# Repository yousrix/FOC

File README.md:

# FOC
bldc driver for foc motor

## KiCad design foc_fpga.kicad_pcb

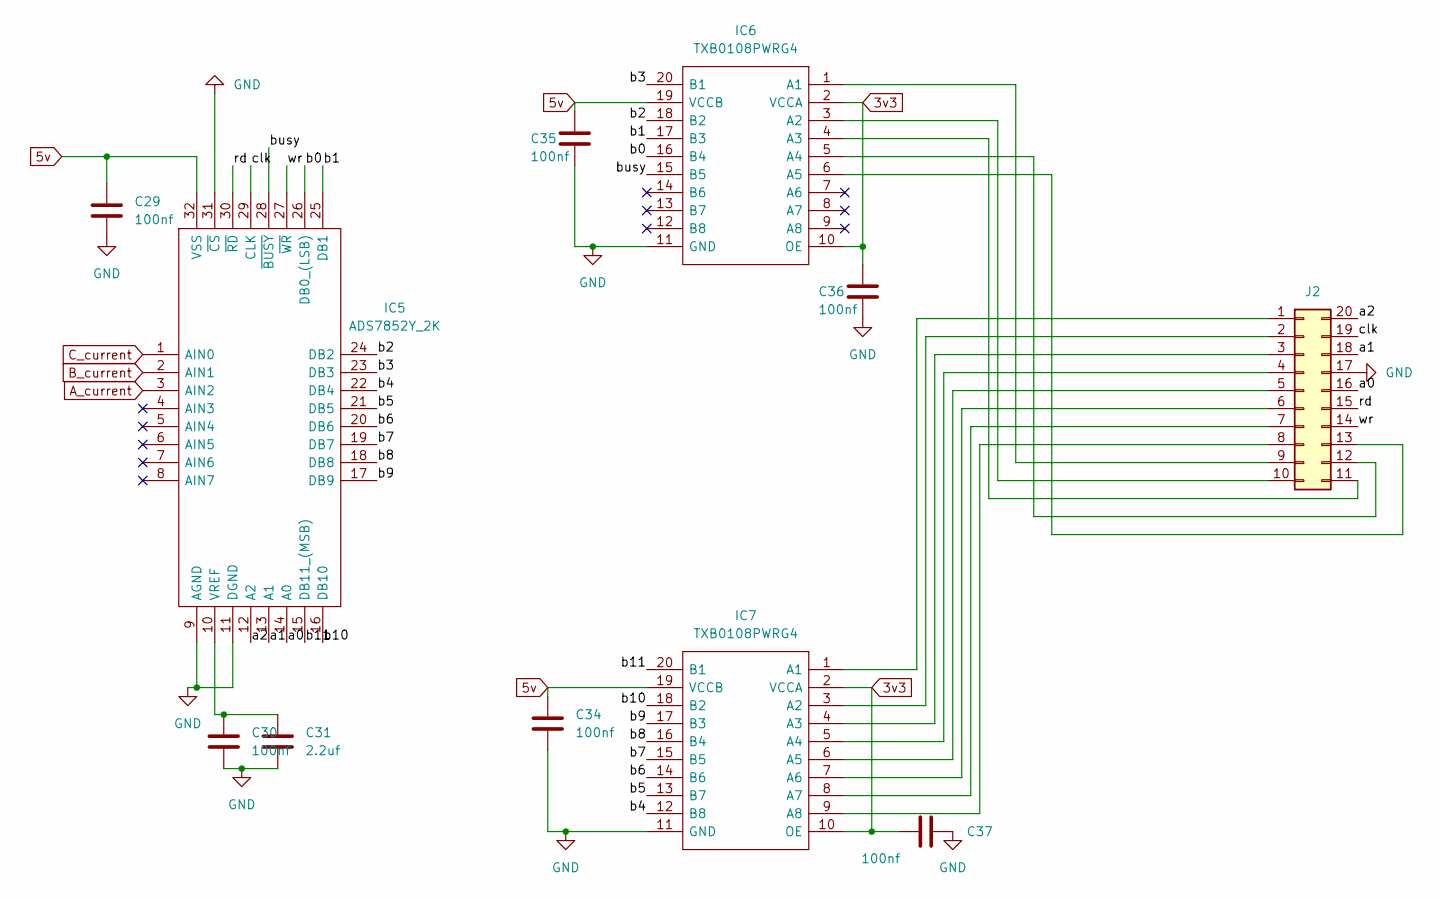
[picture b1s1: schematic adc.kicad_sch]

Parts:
C29, C30, C34, C35, C36, C37: 100nf; C_0402_1005Metric
C31: 2.2uf; C_0402_1005Metric
IC5: ADS7852Y_2K; QFP50P700X700X120-32N; Manufacturer_Part_Number ADS7852Y/2K; Mouser Part Number 595-ADS7852Y/2K
IC6, IC7: TXB0108PWRG4; SOP65P640X120-20N; Manufacturer_Part_Number TXB0108PWRG4; Mouser Part Number 595-TXB0108PWRG4
J2: Conn_02x10_Counter_Clockwise; PinHeader_2x10_P1.00mm_Vertical_SMD

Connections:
3v3: C36.1, C37.1, IC6.2 (VCCA), IC6.10 (OE), IC7.2 (VCCA), IC7.10 (OE); also elsewhere on the board
5v: C29.1, C34.1, C35.1, IC5.32 (VSS), IC6.19 (VCCB), IC7.19 (VCCB); also elsewhere on the board
/adc/a0: IC5.14 (A0), J2.16
/adc/a1: IC5.13 (A1), J2.18
/adc/a2: IC5.12 (A2), J2.20
/adc/b0: IC5.26 (DB0_(LSB)), IC6.16 (B4)
/adc/b1: IC5.25 (DB1), IC6.17 (B3)
/adc/b2: IC5.24 (DB2), IC6.18 (B2)
/adc/b3: IC5.23 (DB3), IC6.20 (B1)
/adc/b4: IC5.22 (DB4), IC7.12 (B8)
/adc/b5: IC5.21 (DB5), IC7.13 (B7)
/adc/b6: IC5.20 (DB6), IC7.14 (B6)
/adc/b7: IC5.19 (DB7), IC7.15 (B5)
/adc/b8: IC5.18 (DB8), IC7.16 (B4)
/adc/b9: IC5.17 (DB9), IC7.17 (B3)
/adc/b10: IC5.16 (DB10), IC7.18 (B2)
/adc/b11: IC5.15 (DB11_(MSB)), IC7.20 (B1)
/adc/busy: IC5.28 (~BUSY), IC6.15 (B5)
/adc/clk: IC5.29 (CLK), J2.19
/adc/rd: IC5.30 (~RD), J2.15
/adc/wr: IC5.27 (~WR), J2.14
A_current: IC5.3 (AIN2); also elsewhere on the board
B_current: IC5.2 (AIN1); also elsewhere on the board
C_current: IC5.1 (AIN0); also elsewhere on the board
GND: C29.2, C30.2, C31.2, C34.2, C35.2, C36.2, C37.2, IC5.9 (AGND), IC5.11 (DGND), IC5.31 (~CS), IC6.11 (GND), IC7.11 (GND), J2.17; also elsewhere on the board
unnamed: C30.1, C31.1, IC5.10 (VREF)
unnamed: IC6.1 (A1), J2.9
unnamed: IC6.3 (A2), J2.10
unnamed: IC6.4 (A3), J2.11
unnamed: IC6.5 (A4), J2.12
unnamed: IC6.6 (A5), J2.13
unnamed: IC7.1 (A1), J2.1
unnamed: IC7.3 (A2), J2.2
unnamed: IC7.4 (A3), J2.3
unnamed: IC7.5 (A4), J2.4
unnamed: IC7.6 (A5), J2.5
unnamed: IC7.7 (A6), J2.6
unnamed: IC7.8 (A7), J2.7
unnamed: IC7.9 (A8), J2.8

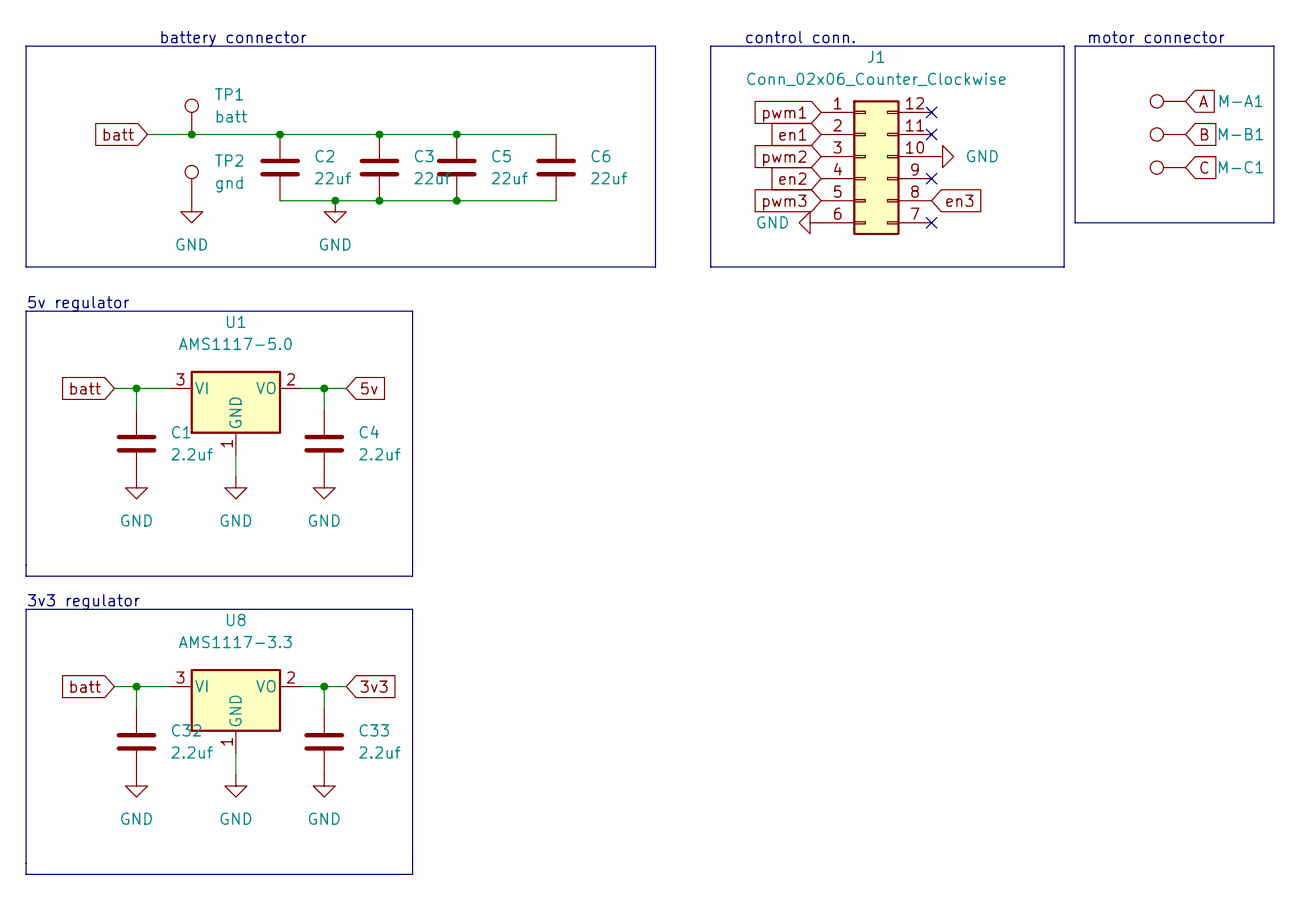
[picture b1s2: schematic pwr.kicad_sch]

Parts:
C1, C4, C32, C33: 2.2uf; C_0603_1608Metric
C2, C3, C5, C6: 22uf; C_0603_1608Metric
J1: Conn_02x06_Counter_Clockwise; PinHeader_2x06_P1.00mm_Vertical_SMD
M-A1: TestPoint; TestPoint_Pad_D2.5mm
M-B1: TestPoint; TestPoint_Pad_D2.5mm
M-C1: TestPoint; TestPoint_Pad_D2.5mm
TP1: batt; TestPoint_Pad_D1.5mm
TP2: gnd; TestPoint_Pad_D1.5mm
U1: AMS1117-5.0; SOT-223-3_TabPin2
U8: AMS1117-3.3; SOT-223-3_TabPin2

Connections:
3v3: C33.1, U8.2 (VO); also elsewhere on the board
5v: C4.1, U1.2 (VO); also elsewhere on the board
A: M-A1.1; also elsewhere on the board
B: M-B1.1; also elsewhere on the board
C: M-C1.1; also elsewhere on the board
GND: C1.2, C2.2, C3.2, C4.2, C5.2, C6.2, C32.2, C33.2, J1.6, J1.10, TP2.1, U1.1 (GND), U8.1 (GND); also elsewhere on the board
batt: C1.1, C2.1, C3.1, C5.1, C6.1, C32.1, TP1.1, U1.3 (VI), U8.3 (VI); also elsewhere on the board
en1: J1.2; also elsewhere on the board
en2: J1.4; also elsewhere on the board
en3: J1.8; also elsewhere on the board
pwm1: J1.1; also elsewhere on the board
pwm2: J1.3; also elsewhere on the board
pwm3: J1.5; also elsewhere on the board

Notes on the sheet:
5v regulator
battery connector
3v3 regulator
motor connector
control conn.

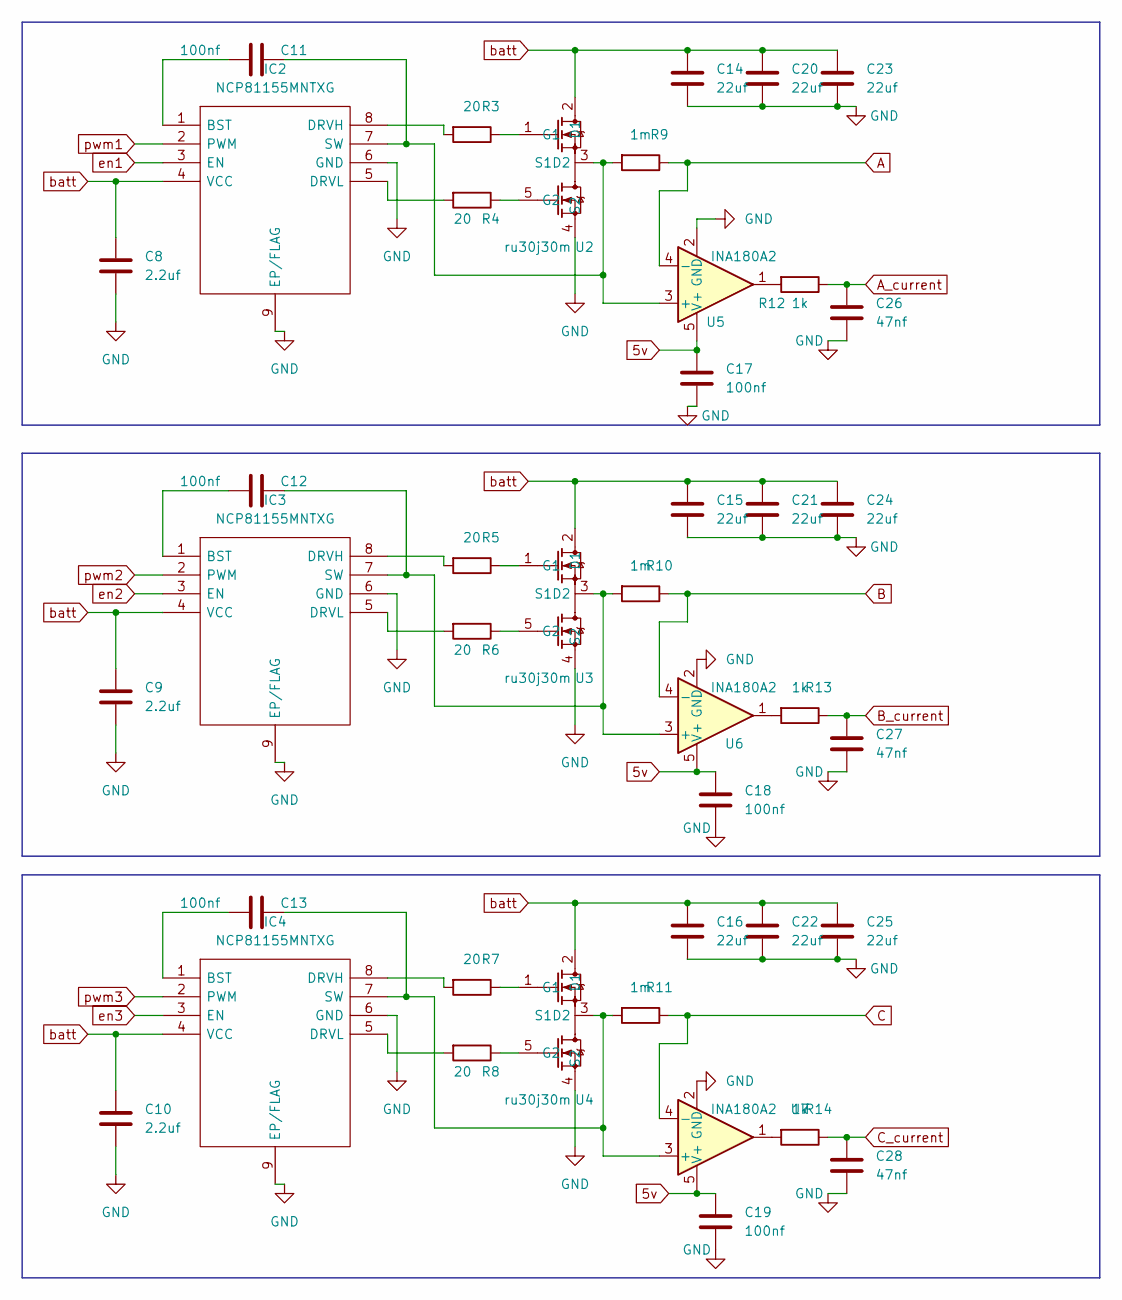
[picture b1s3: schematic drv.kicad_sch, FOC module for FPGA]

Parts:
C8, C9, C10: 2.2uf; C_0402_1005Metric
C11, C12, C13, C17, C18, C19: 100nf; C_0402_1005Metric
C14, C15, C16, C20, C21, C22, C23, C24, C25: 22uf; C_0603_1608Metric
C26, C27, C28: 47nf; C_0402_1005Metric
IC2, IC3, IC4: NCP81155MNTXG; SON50P300X300X100-9N-D; Manufacturer_Part_Number NCP81155MNTXG; Mouser Part Number 863-NCP81155MNTXG
R3, R4, R5, R6, R7, R8: 20; R_0402_1005Metric
R9, R10, R11: 1m; R_2512_6332Metric; lcsc C2903470
R12, R13, R14: 1k; R_0402_1005Metric
U2, U3, U4: ru30j30m; pdfn5060
U5, U6, U7: INA180A2; SOT-23-5

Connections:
5v: C17.1, C18.1, C19.1, U5.5 (V+), U6.5 (V+), U7.5 (V+); also elsewhere on the board
A: R9.1, U5.4 (-); also elsewhere on the board
A_current: C26.1, R12.1; also elsewhere on the board
B: R10.1, U6.4 (-); also elsewhere on the board
B_current: C27.1, R13.1; also elsewhere on the board
C: R11.1, U7.4 (-); also elsewhere on the board
C_current: C28.1, R14.1; also elsewhere on the board
GND: C8.2, C9.2, C10.2, C14.2, C15.2, C16.2, C17.2, C18.2, C19.2, C20.2, C21.2, C22.2, C23.2, C24.2, C25.2, C26.2, C27.2, C28.2, IC2.6 (GND), IC2.9 (EP/FLAG), IC3.6 (GND), IC3.9 (EP/FLAG), IC4.6 (GND), IC4.9 (EP/FLAG), U2.4 (S2), U3.4 (S2), U4.4 (S2), U5.2 (GND), U6.2 (GND), U7.2 (GND); also elsewhere on the board
unnamed: C11.1, IC2.1 (BST)
unnamed: C11.2, IC2.7 (SW), R9.2, U2.3 (S1D2), U5.3 (+)
unnamed: C12.1, IC3.1 (BST)
unnamed: C12.2, IC3.7 (SW), R10.2, U3.3 (S1D2), U6.3 (+)
unnamed: C13.1, IC4.1 (BST)
unnamed: C13.2, IC4.7 (SW), R11.2, U4.3 (S1D2), U7.3 (+)
unnamed: IC2.5 (DRVL), R4.2
unnamed: IC2.8 (DRVH), R3.2
unnamed: IC3.5 (DRVL), R6.2
unnamed: IC3.8 (DRVH), R5.2
unnamed: IC4.5 (DRVL), R8.2
unnamed: IC4.8 (DRVH), R7.2
unnamed: R3.1, U2.1 (G1)
unnamed: R4.1, U2.5 (G2)
unnamed: R5.1, U3.1 (G1)
unnamed: R6.1, U3.5 (G2)
unnamed: R7.1, U4.1 (G1)
unnamed: R8.1, U4.5 (G2)
unnamed: R12.2, U5.1
unnamed: R13.2, U6.1
unnamed: R14.2, U7.1
batt: C8.1, C9.1, C10.1, C14.1, C15.1, C16.1, C20.1, C21.1, C22.1, C23.1, C24.1, C25.1, IC2.4 (VCC), IC3.4 (VCC), IC4.4 (VCC), U2.2 (D1), U3.2 (D1), U4.2 (D1); also elsewhere on the board
en1: IC2.3 (EN); also elsewhere on the board
en2: IC3.3 (EN); also elsewhere on the board
en3: IC4.3 (EN); also elsewhere on the board
pwm1: IC2.2 (PWM); also elsewhere on the board
pwm2: IC3.2 (PWM); also elsewhere on the board
pwm3: IC4.2 (PWM); also elsewhere on the board

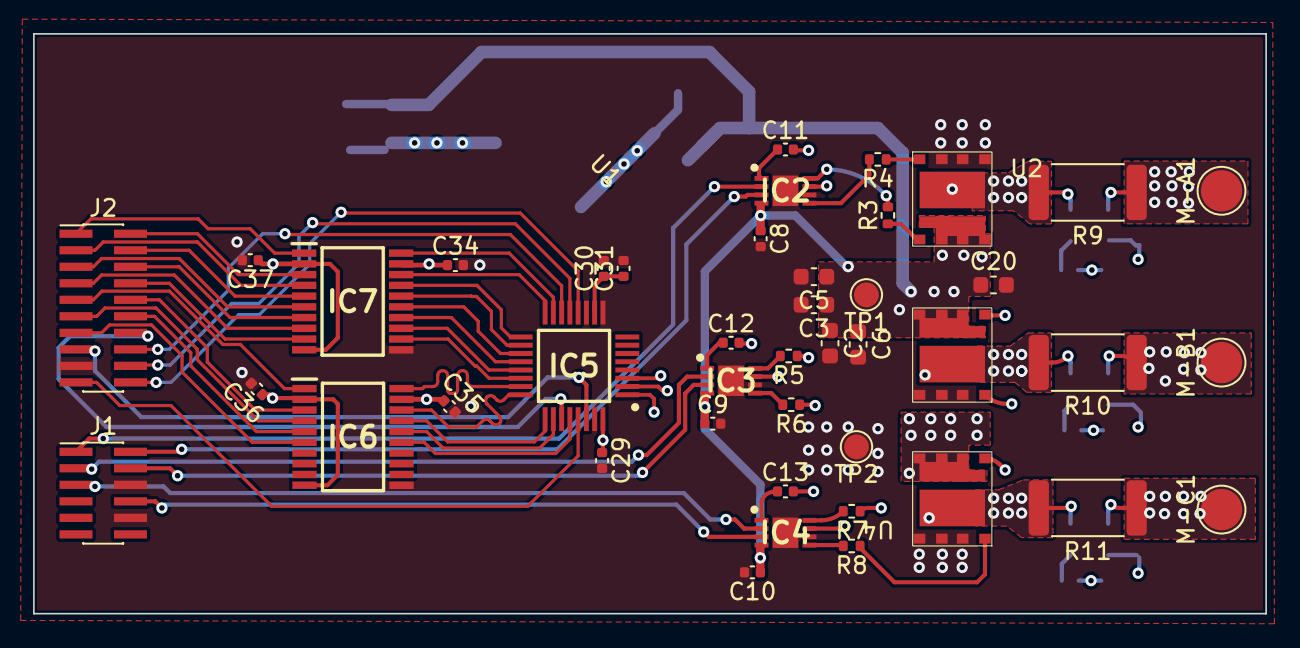
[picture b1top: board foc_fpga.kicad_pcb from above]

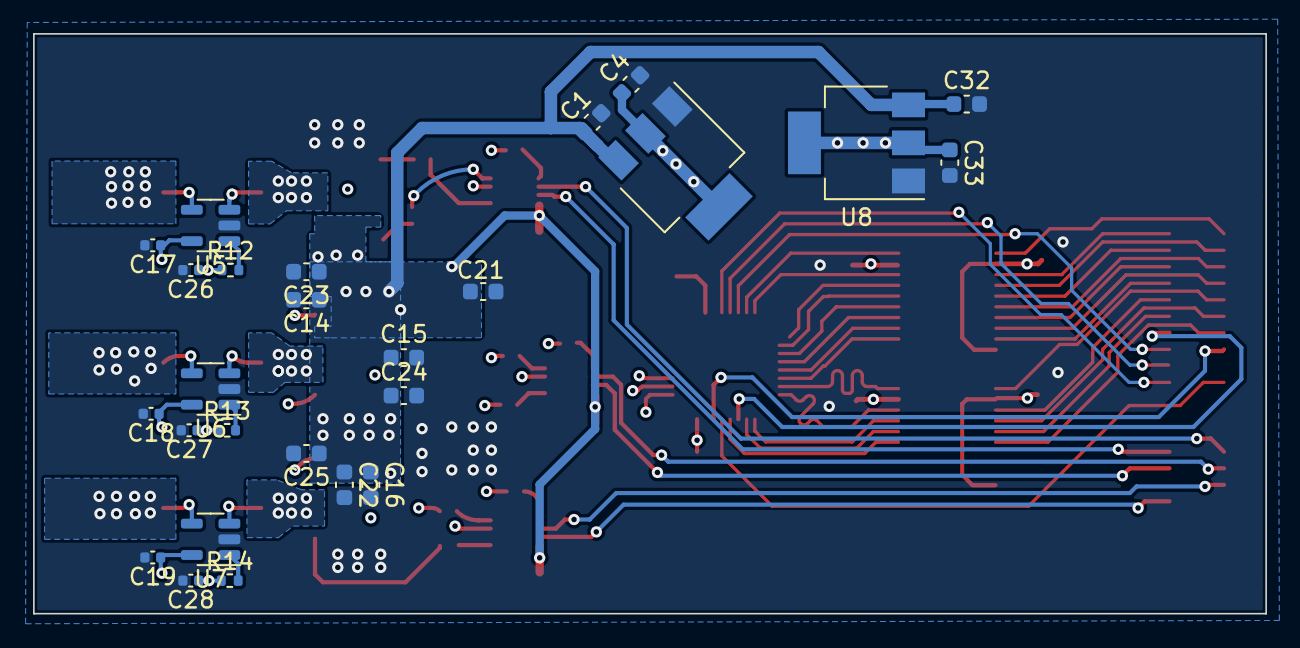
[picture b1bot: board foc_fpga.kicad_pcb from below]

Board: 4 copper layers, 74.6 x 35.1 mm, 69 parts (26 on the bottom side), 70 nets.
